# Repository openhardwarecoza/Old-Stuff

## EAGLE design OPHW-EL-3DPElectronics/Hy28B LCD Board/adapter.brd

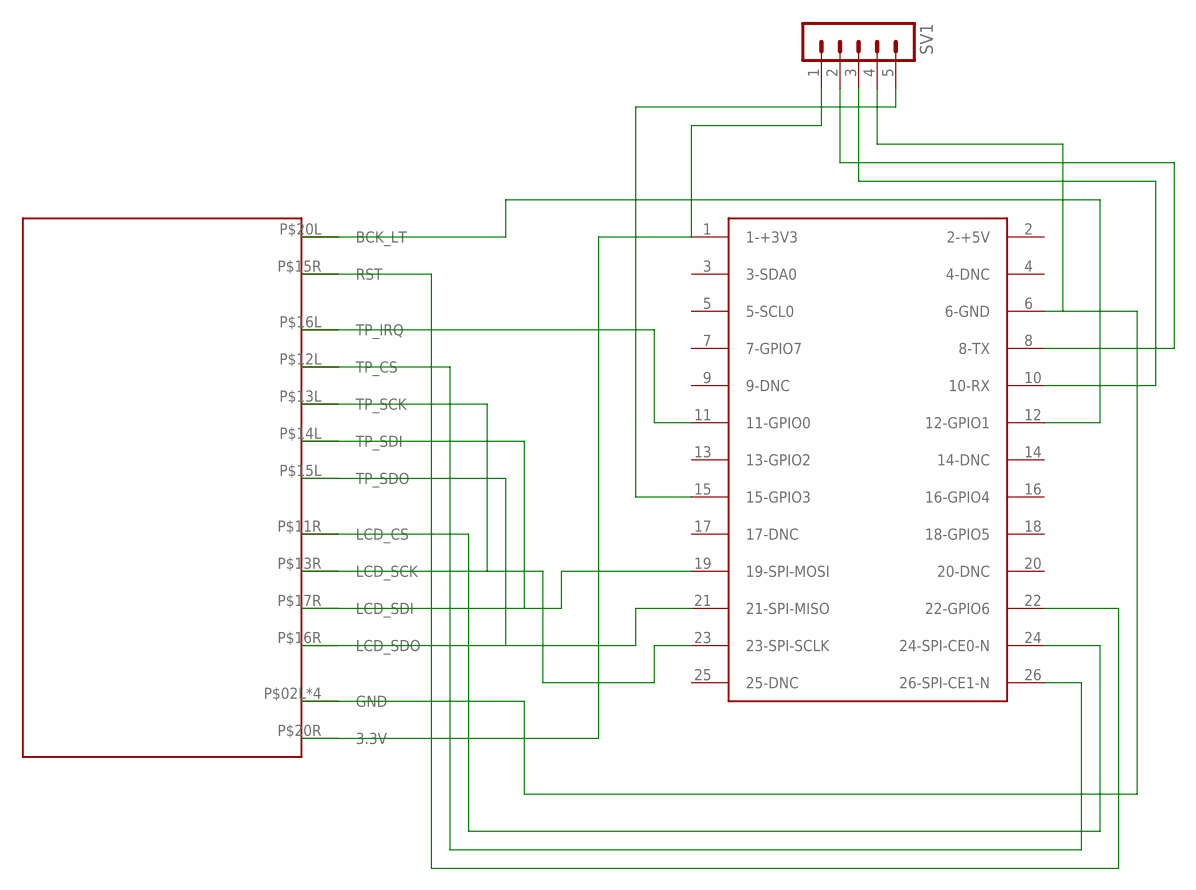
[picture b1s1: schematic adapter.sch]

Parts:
SV1: MA05-1
U$1: HY28BSTD; HY28B
U$2: RASPBERRY-PI

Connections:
unnamed: SV1.1, U$1.P$20R (3.3V), U$2.1 (1-+3V3)
unnamed: SV1.4, U$1.P$02L (GND), U$1.P$02R (GND), U$1.P$19L (GND), U$1.P$19R (GND), U$2.6 (6-GND)
unnamed: U$1.P$15L (TP_SDO), U$1.P$16R (LCD_SDO), U$2.21 (21-SPI-MISO)
unnamed: U$1.P$14L (TP_SDI), U$1.P$17R (LCD_SDI), U$2.19 (19-SPI-MOSI)
unnamed: U$1.P$13L (TP_SCK), U$1.P$13R (LCD_SCK), U$2.23 (23-SPI-SCLK)
unnamed: U$1.P$11R (LCD_CS), U$2.24 (24-SPI-CE0-N)
unnamed: U$1.P$12L (TP_CS), U$2.26 (26-SPI-CE1-N)
unnamed: U$1.P$16L (TP_IRQ), U$2.11 (11-GPIO0)
unnamed: U$1.P$20L (BCK_LT), U$2.12 (12-GPIO1)
unnamed: U$1.P$15R (RST), U$2.22 (22-GPIO6)
unnamed: SV1.2, U$2.8 (8-TX)
unnamed: SV1.3, U$2.10 (10-RX)
unnamed: SV1.5, U$2.15 (15-GPIO3)

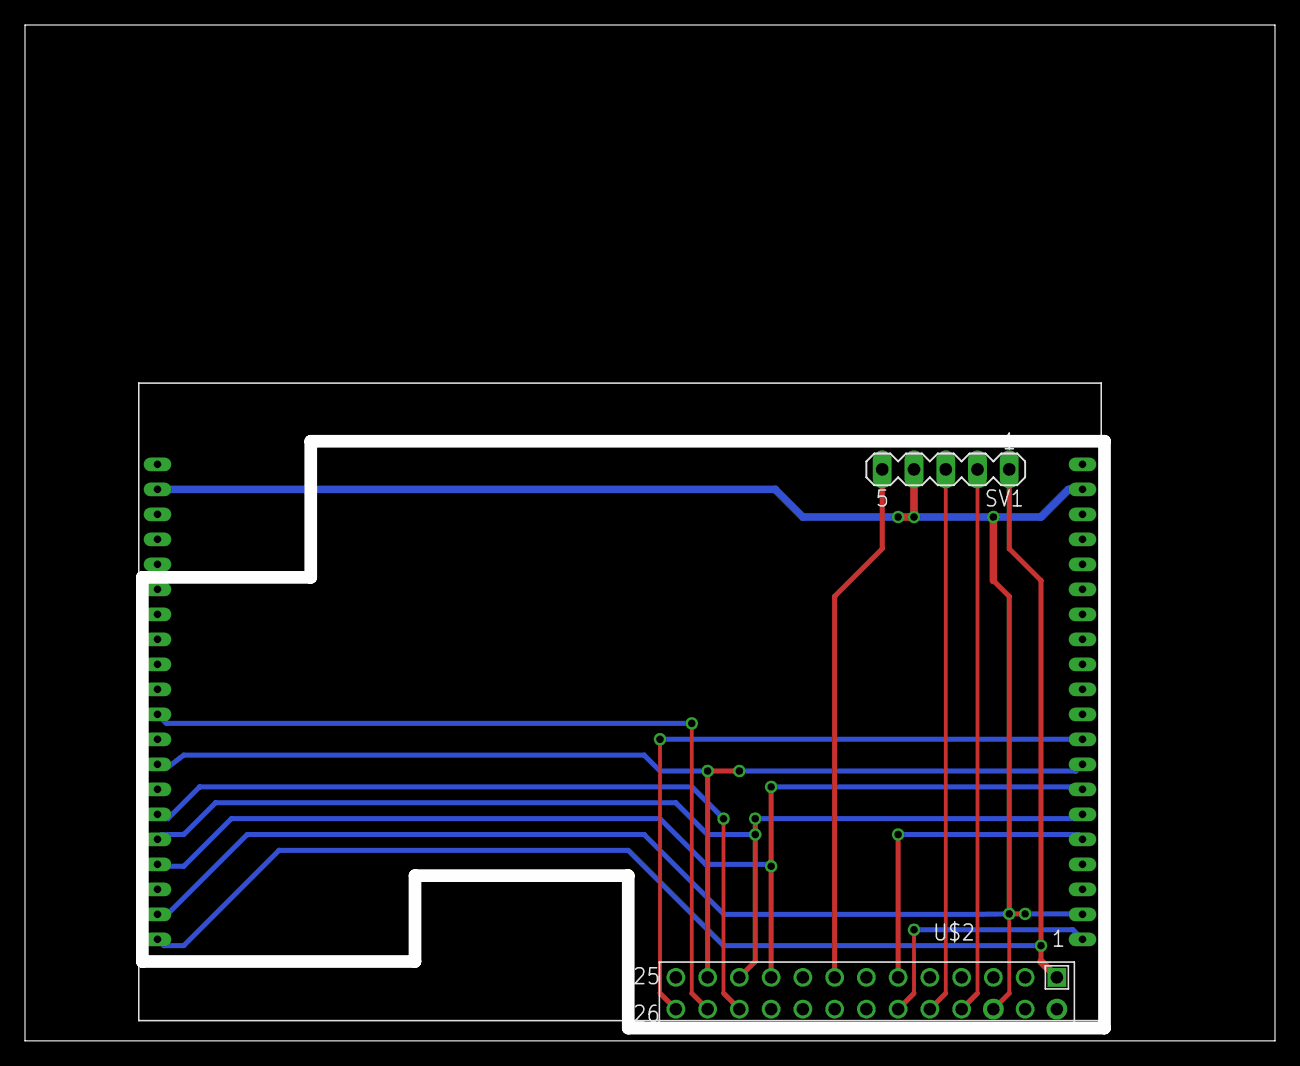
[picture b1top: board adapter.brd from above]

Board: 2 copper layers, 100.0 x 81.3 mm, 3 parts (0 on the bottom side), 13 nets.

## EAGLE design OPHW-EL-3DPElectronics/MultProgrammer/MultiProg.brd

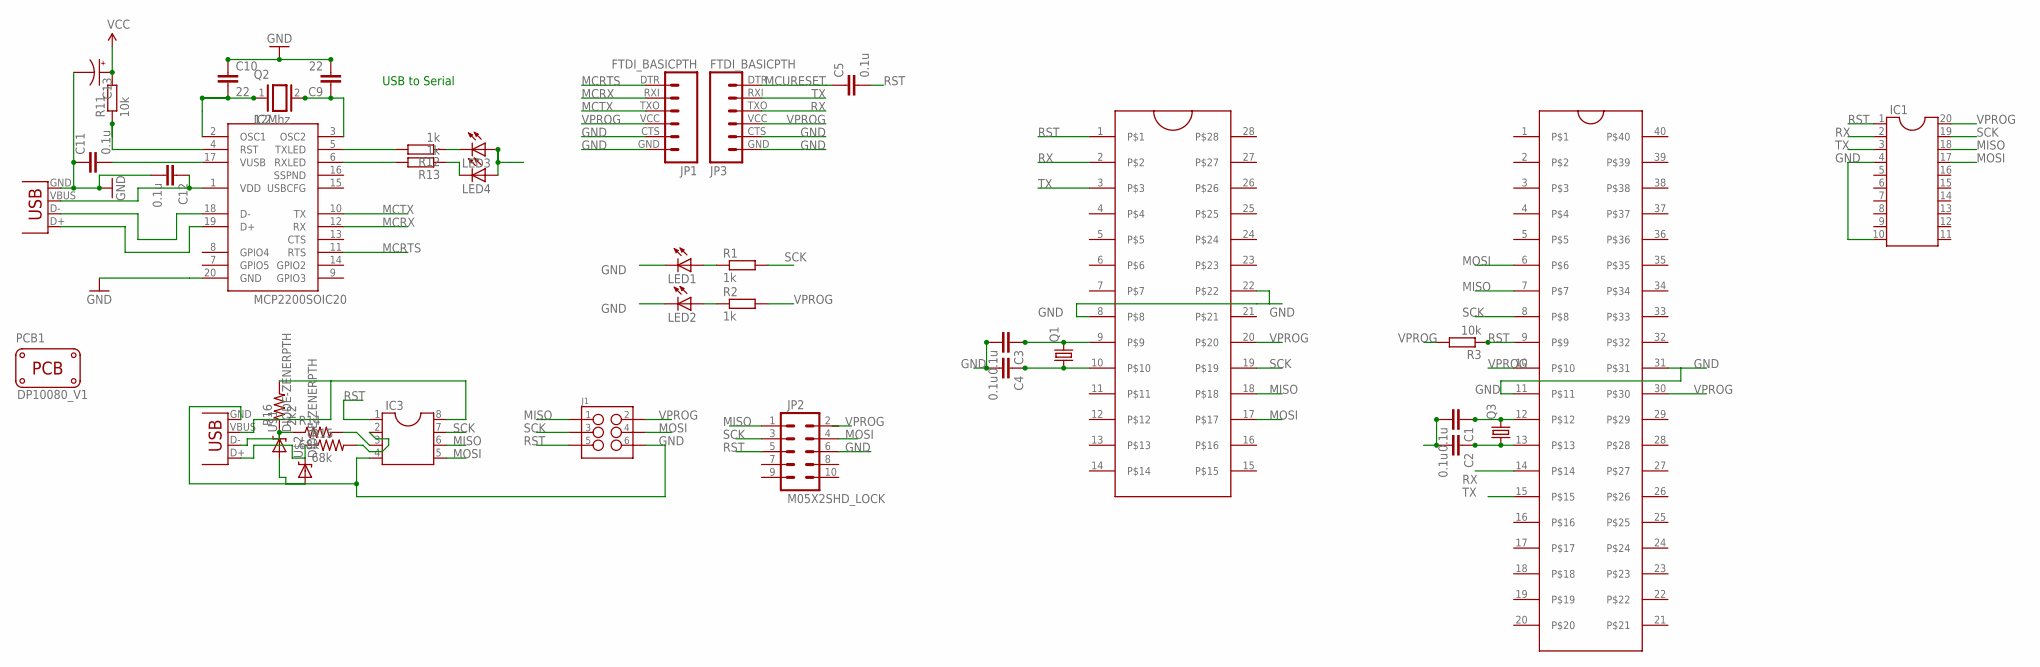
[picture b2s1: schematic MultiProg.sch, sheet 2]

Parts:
C1, C2, C3, C4, C5, C11, C12: 0.1u; CAP-PTH-SMALL-KIT
C9, C10: 22; CAP-PTH-SMALL-KIT
C13: CAP_POLPTH1; CPOL-RADIAL-100UF-25V
IC1: DIL20
IC2: MCP2200SOIC20; SOIC20
IC3: DIL8; DIL08
J1: M03X2SHROUD; 2X3-SHROUDED
JP1, JP3: FTDI_BASICPTH; FTDI_BASIC
JP2: M05X2SHD_LOCK; 2X5-SHROUDED_LOCK
LED1, LED2, LED3, LED4: LED3MM
PCB1: PCB_DP_RECTANGLE-80X100; DP10080_V1
Q1, Q3: CRYSTALHC49U70; HC49U70
Q2: 12Mhz; QS
R1, R2, R12, R13: 1k; 0204/7
R3, R11: 10k; 0204/7
R14, R15: 68k; 0204/7
R16: 2k2; 0204/7
U$1, U$2: DIODE-ZENERPTH; DIODE-ZENER
U$3: ZIFSOCKET-28-3ZIFFSOCKET-28-3; DIL28-3-ZIF_SOCKET
U$4: ZIFSOCKET-40-6DIL40-6-ZIF_SOCKET; DIL40-6-ZIF_SOCKET
X1, X3: USBPTH; USB-B-PTH

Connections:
D+: R15.1, U$2.P$1 (C), X3.D+
D-: R14.1, R16.1, U$1.P$1 (C), X3.D-
GND: C1.2, C2.2, C3.2, C4.2, C9.2, C10.1, C11.1, C12.2, C13.2 (-), IC1.4, IC1.10, IC2.20 (GND), IC3.4, J1.6, JP1.CTS (5), JP1.GND (6), JP2.6, JP3.CTS (5), JP3.GND (6), LED1.K (C), LED2.K (C), U$1.P$2 (A), U$2.P$2 (A), U$3.8, U$3.22, U$4.11, U$4.31, X1.GND, X3.GND
MCRTS: IC2.11 (RTS), JP1.DTR (1)
MCRX: IC2.12 (RX), JP1.RXI (2)
MCTX: IC2.10 (TX), JP1.TXO (3)
MCURESET: C5.1, JP3.DTR (1)
MISO: IC1.18, IC3.6, J1.1, JP2.1, U$3.18, U$4.7
MOSI: IC1.17, IC3.5, J1.4, JP2.4, U$3.17, U$4.6
unnamed: IC3.3, R14.2
unnamed: C10.2, IC2.2 (OSC1), Q2.1
unnamed: C9.1, IC2.3 (OSC2), Q2.2
unnamed: IC2.18 (D-), X1.D-
unnamed: IC2.19 (D+), X1.D+
unnamed: C11.2, IC2.17 (VUSB)
unnamed: IC2.5 (TXLED), R12.2
unnamed: IC2.6 (RXLED), R13.2
unnamed: LED3.K (C), R12.1
unnamed: LED4.K (C), R13.1
unnamed: IC2.4 (RST), R11.1
unnamed: IC3.2, R15.2
unnamed: LED2.A, R2.1
unnamed: LED1.A, R1.1
unnamed: C1.1, Q3.2, U$4.12
unnamed: C2.1, Q3.1, U$4.13
unnamed: C3.1, Q1.2, U$3.9
unnamed: C4.1, Q1.1, U$3.10
RST: C5.2, IC1.1, IC3.1, J1.5, JP2.5, R3.1, U$3.1, U$4.9
RX: IC1.2, JP3.TXO (3), U$3.2, U$4.14
SCK: IC1.19, IC3.7, J1.3, JP2.3, R1.2, U$3.19, U$4.8
TX: IC1.3, JP3.RXI (2), U$3.3, U$4.15
VBUS: C12.1, IC2.1 (VDD), LED3.A, LED4.A, X1.VBUS
VPROG: C13.1 (+), IC1.20, IC3.8, J1.2, JP1.VCC (4), JP3.VCC (4), R2.2, R3.2, R11.2, R16.2, U$3.20, U$4.10, U$4.30, X3.VBUS

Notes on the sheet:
USB to Serial

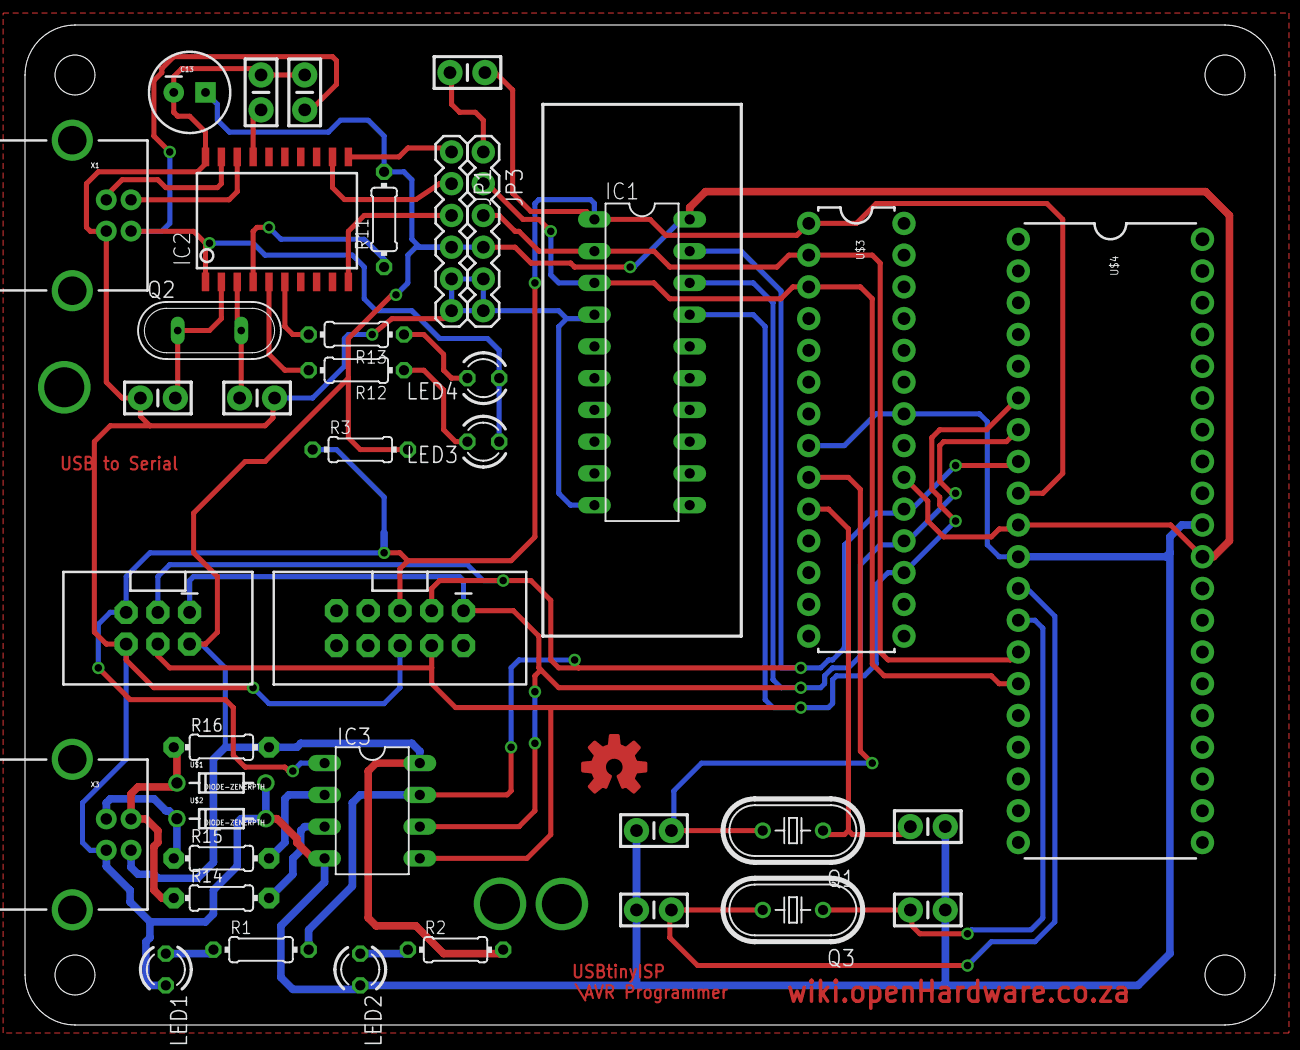
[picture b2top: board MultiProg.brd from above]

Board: 2 copper layers, 100.0 x 80.0 mm, 41 parts (0 on the bottom side), 33 nets.

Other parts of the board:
U$5: OSHWLOGO_TOP_0.2

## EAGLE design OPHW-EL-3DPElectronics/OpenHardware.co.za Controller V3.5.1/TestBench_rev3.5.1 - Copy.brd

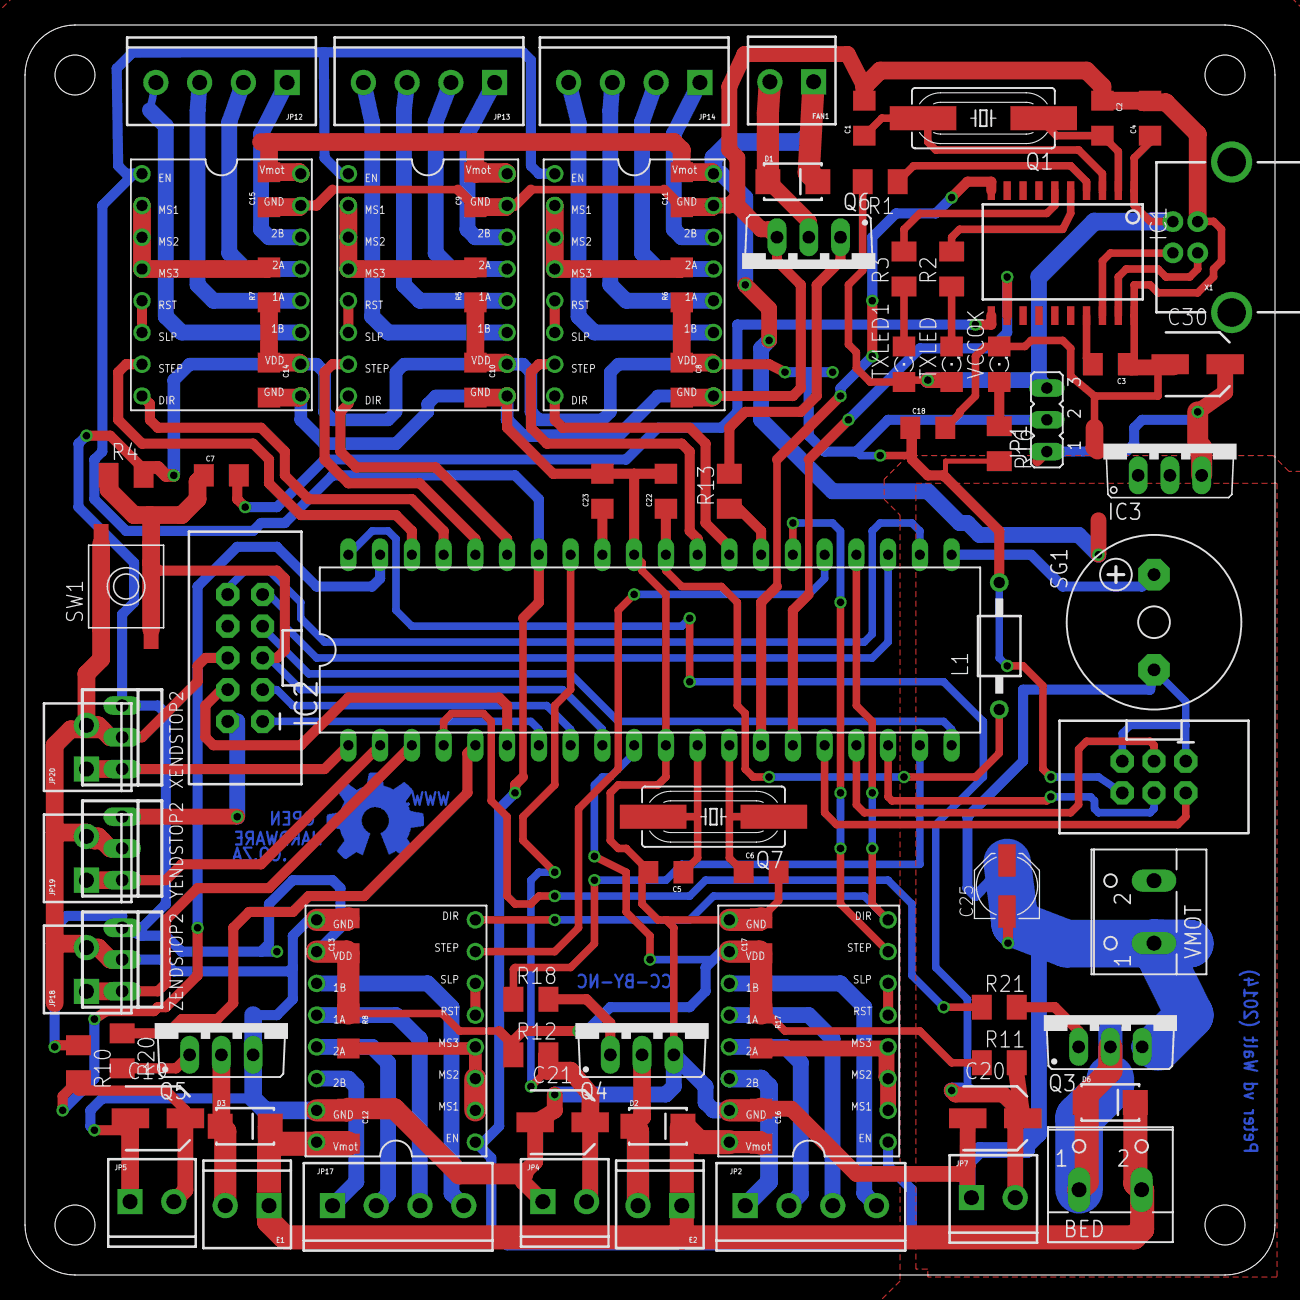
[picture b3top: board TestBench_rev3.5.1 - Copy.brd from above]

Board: 2 copper layers, 100.0 x 100.0 mm, 91 parts (0 on the bottom side), 92 nets.

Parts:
BED: W237-102
C1, C2, C5, C6: 22; 1206
C3, C4, C7, C18, C22, C23: 0.1u; 1206
C8, C9, C10, C11, C12, C13, C14, C15, C16, C17: 1206
C19, C20, C21, C30: 10u; SANYO-OSCON_SMD_B6
C25: 100u; PANASONIC_C
D1, D2, D3, D6: SMA-DIODE_ALT
E1: E1; SCREWTERMINAL-3.5MM-2
E1POL, E2POL: POLOLU_A4983CARRIER; A4988BREAKOUT
E2: E2; SCREWTERMINAL-3.5MM-2
FAN1: FAN; SCREWTERMINAL-3.5MM-2
IC1: MCP2200SOIC20; SOIC20
IC2: ATMEGA644-20PU; DIL40
IC3: 7805TV; TO220V
JP1: JP2
JP2, JP12, JP13, JP14, JP17: SCREWTERMINAL-3.5MM-4
JP3: 2X3-SHROUDED
JP4, JP5, JP7, JP18, JP19, JP20: SCREWTERMINAL-3.5MM-2
JP6: M05X2SHD_LOCK; 2X5-SHROUDED_LOCK
L1: 10uH; BL01RN1A
PCB1: PCB_DP_SQUARE-10X10; DP100100_V1
Q1: 12Mhz; HC49UP
Q3, Q4, Q5, Q6: TO220BV
Q7: 20Mhz; HC49UP
R1, R4: 10k; M1206
R2, R3, R16: 1k; M1206
R5, R6, R7, R8, R17: 1206
R10, R11, R12: 4k7; M1206
R13, R18, R20, R21: 10R; M1206
SG1: F/CM12P
SW1: SPST_TACT-EVQQ2; EVQ-Q2
TXLED, TXLED1: 1206
U$1: LABEL_JUMPER_1X3; JUMP3_DESC
VCCOK: 1206
VMOT: W237-102
X1: USBPTH; USB-B-PTH
XENDSTOP2: 22-23-2031
XPOL: POLOLU_A4983CARRIER; A4988BREAKOUT
YENDSTOP2: 22-23-2031
YPOL: POLOLU_A4983CARRIER; A4988BREAKOUT
ZENDSTOP2: 22-23-2031
ZPOL: POLOLU_A4983CARRIER; A4988BREAKOUT

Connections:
5VREG: C30.+, IC3.3, JP1.1
AVCC: C22.1, IC2.30, L1.1
BEDADC: C20.+, IC2.40, JP7.2, R11.2
BEDMSFT: IC2.4, R21.1
BEDOUT1: BED.1, D6.A, Q3.D
BEDOUT2: D3.A, E1.2, Q5.D
BUZZER: IC2.21, SG1.+
E1DIR: E1POL.DIR, E2POL.DIR, IC2.24
E1OUT1: D2.A, E2.2, Q4.D
E1STEP: E1POL.STEP, IC2.25
E2MSFT: IC2.19, R18.1
E2STEP: E2POL.STEP, IC2.26
ENABLE: E1POL.EN, E2POL.EN, IC2.34, XPOL.EN, YPOL.EN, ZPOL.EN
ENCA: IC2.16, JP3.2
ENCB: IC2.17, JP3.3
ENCC: IC2.18, JP3.4
EXT2ADC: C21.+, IC2.33, JP4.2, R12.2
EXTADC: C19.+, IC2.39, JP5.2, R10.2
EXTMSFT: IC2.5, R20.1
FANMSFT: IC2.27, R13.1
FANOUT1: D1.A, FAN1.2, Q6.D
GND: C1.2, C2.1, C3.1, C4.2, C5.2, C6.2, C8.2, C9.1, C10.2, C11.1, C12.1, C13.2, C14.2, C15.1, C16.1, C17.2, C18.2, C19.-, C20.-, C21.-, C22.2, C23.2, C25.-, C30.-, E1POL.GND, E1POL.GND@0, E2POL.GND, E2POL.GND@0, IC1.20, IC2.11, IC2.31, IC3.2, JP3.1, JP3.5, JP4.1, JP5.1, JP6.6, JP7.1, JP18.2, JP19.2, JP20.2, Q3.S, Q4.S, Q5.S, Q6.S, SG1.-, SW1.B, SW1.B', VCCOK.C, VMOT.1, X1.GND, XENDSTOP2.2, XPOL.GND, XPOL.GND@0, YENDSTOP2.2, YPOL.GND, YPOL.GND@0, ZENDSTOP2.2, ZPOL.GND, ZPOL.GND@0
MCRTS: C7.2, IC1.11
MCRX: IC1.12, IC2.15
MCTX: IC1.10, IC2.14
MCURESET: C7.1, IC2.9, JP6.5, R4.1, SW1.A, SW1.A'
MISO: IC2.7, JP6.1
MOSI: IC2.6, JP6.4
unnamed: C2.2, IC1.2, Q1.1
unnamed: C1.1, IC1.3, Q1.2
unnamed: IC1.5, R2.2
unnamed: IC1.18, X1.D-
unnamed: IC1.19, X1.D+
unnamed: IC1.6, R3.2
unnamed: C3.2, IC1.17
unnamed: E2POL.RST, E2POL.SLP
unnamed: R2.1, TXLED.C
unnamed: R3.1, TXLED1.C
unnamed: C5.1, IC2.12, Q7.2
unnamed: C6.1, IC2.13, Q7.1
unnamed: IC1.4, R1.1
unnamed: E1POL.RST, E1POL.SLP
unnamed: ZPOL.RST, ZPOL.SLP
unnamed: YPOL.RST, YPOL.SLP
unnamed: XPOL.RST, XPOL.SLP
unnamed: R7.2, XPOL.MS1, XPOL.MS2, XPOL.MS3
unnamed: R5.2, YPOL.MS1, YPOL.MS2, YPOL.MS3
unnamed: E1POL.MS1, E1POL.MS2, E1POL.MS3, R8.2
unnamed: R6.2, ZPOL.MS1, ZPOL.MS2, ZPOL.MS3
unnamed: E1POL.1B, JP17.4
unnamed: E1POL.1A, JP17.3
unnamed: E1POL.2A, JP17.2
unnamed: E1POL.2B, JP17.1
unnamed: JP14.4, ZPOL.1B
unnamed: JP14.3, ZPOL.1A
unnamed: JP14.2, ZPOL.2A
unnamed: JP14.1, ZPOL.2B
unnamed: JP13.1, YPOL.2B
unnamed: JP13.2, YPOL.2A
unnamed: JP13.3, YPOL.1A
unnamed: JP13.4, YPOL.1B
unnamed: JP12.4, XPOL.1B
unnamed: JP12.3, XPOL.1A
unnamed: JP12.2, XPOL.2A
unnamed: JP12.1, XPOL.2B
unnamed: E2POL.MS1, E2POL.MS2, E2POL.MS3, R17.2
unnamed: E2POL.1B, JP2.4
unnamed: E2POL.1A, JP2.3
unnamed: E2POL.2A, JP2.2
unnamed: E2POL.2B, JP2.1
unnamed: Q5.G, R20.2
unnamed: C23.1, IC2.32
unnamed: Q6.G, R13.2
unnamed: Q4.G, R18.2
unnamed: R16.1, VCCOK.A
unnamed: Q3.G, R21.2
SCK: IC2.8, JP6.3
SCL: IC2.22, JP6.10
SDA: IC2.23, JP6.9
SDS: IC2.20, JP6.7
VCC: C8.1, C10.1, C13.1, C14.1, C17.1, C18.1, E1POL.VDD, E2POL.VDD, IC2.10, JP1.2, JP3.6, JP6.2, L1.2, R4.2, R5.1, R6.1, R7.1, R8.1, R10.1, R11.1, R12.1, R16.2, R17.1, XENDSTOP2.1, XPOL.VDD, YENDSTOP2.1, YPOL.VDD, ZENDSTOP2.1, ZPOL.VDD
VMOT: BED.2, C9.2, C11.2, C12.2, C15.2, C16.2, C25.+, D1.C, D2.C, D3.C, D6.C, E1.1, E1POL.VMOT, E2.1, E2POL.VMOT, FAN1.1, IC3.1, VMOT.2, XPOL.VMOT, YPOL.VMOT, ZPOL.VMOT
VUSB: C4.1, IC1.1, JP1.3, R1.2, TXLED.A, TXLED1.A, X1.VBUS
XDIR: IC2.37, XPOL.DIR
XEND: IC2.1, JP20.1, XENDSTOP2.3
XSTEP: IC2.38, XPOL.STEP
YDIR: IC2.35, YPOL.DIR
YEND: IC2.2, JP19.1, YENDSTOP2.3
YSTEP: IC2.36, YPOL.STEP
ZDIR: IC2.28, ZPOL.DIR
ZEND: IC2.3, JP18.1, ZENDSTOP2.3
ZSTEP: IC2.29, ZPOL.STEP

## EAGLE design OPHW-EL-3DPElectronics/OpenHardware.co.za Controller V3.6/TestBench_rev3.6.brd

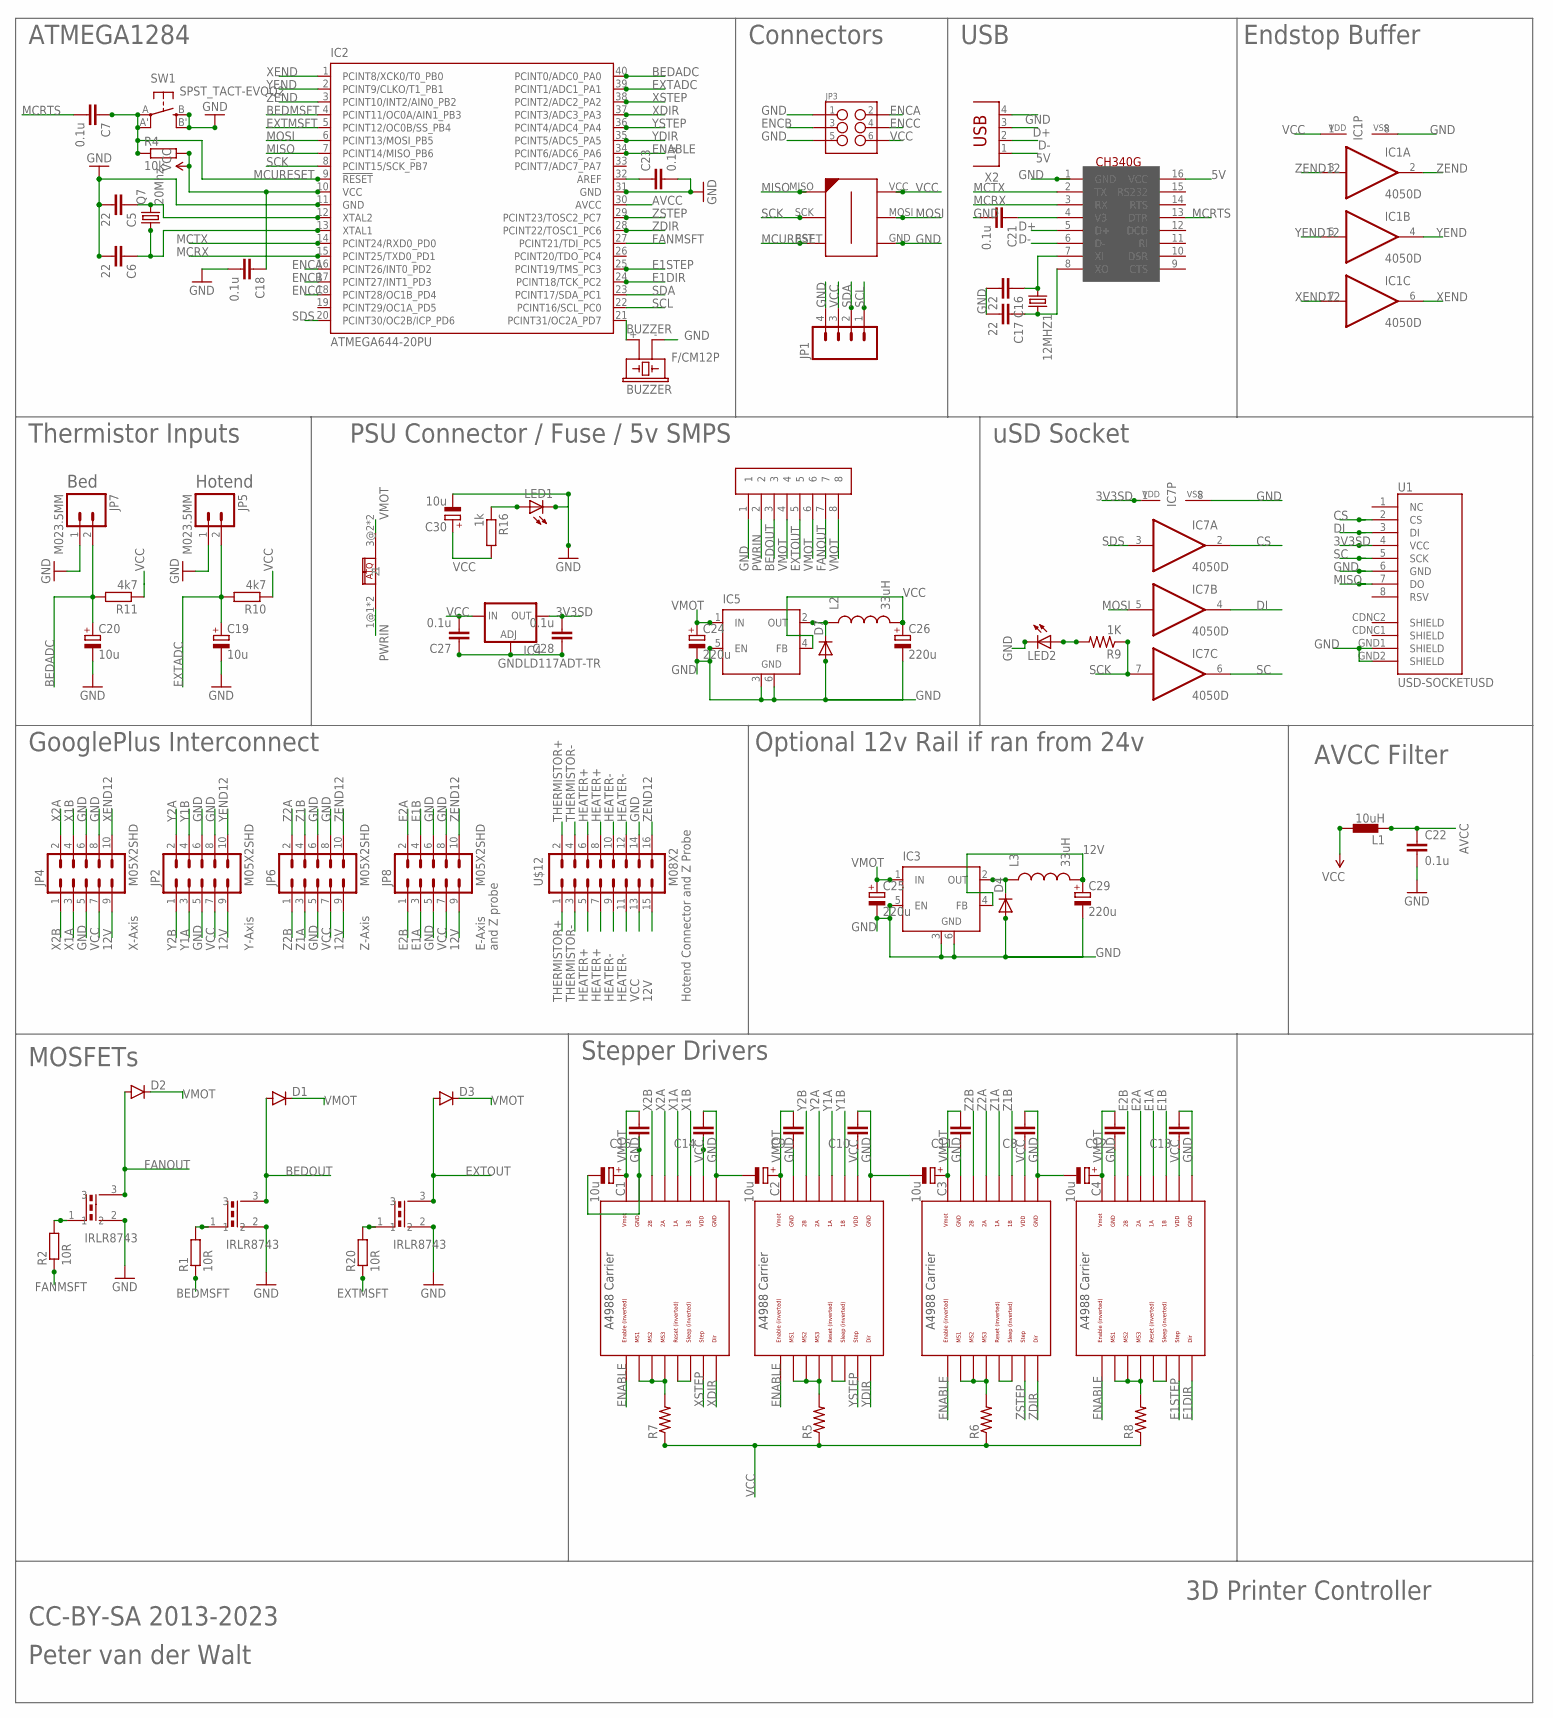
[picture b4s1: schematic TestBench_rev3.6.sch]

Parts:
12MHZ1: CRYSTALHC49UP; HC49UP
BUZZER: F/CM12P
C1, C2, C3, C4, C19, C20, C30: 10u; SANYO-OSCON_SMD_B6
C5, C6, C16, C17: 22; 1206
C7, C18, C21, C22, C23, C27, C28: 0.1u; 1206
C8, C9, C10, C11, C12, C13, C14, C15: CAP1206; 1206
C24, C25, C26, C29: 220u; 153CLV-0605
D1, D2, D3: DIODESMA-ALT; SMA-DIODE_ALT
D4, D7: DIODE-DO-214AC; DO-214AC
E1POL: POLOLU_A4983CARRIER; A4988BREAKOUT
IC1, IC7: 4050D; SO16
IC2: ATMEGA644-20PU; DIL40
IC3, IC5: LM2596S; TO263-5
IC4: LD117ADT-TR; DPACK
JP1: M04LOCK; 1X04_LOCK
JP2, JP4, JP6, JP8: M05X2SHD; 2X5-SHROUDED
JP3: M03X2SHROUD; 2X3-SHROUDED
JP5, JP7: M023.5MM; SCREWTERMINAL-3.5MM-2
L1: 10uH; BL01RN1A
L2, L3: 33uH; CDRH125
LED1, LED2: LEDSMT1206; 1206
Q7: 20Mhz; HC49UP
R1, R2, R20: 10R; M1206
R4: 10k; M1206
R5, R6, R7, R8: RESISTOR1206; 1206
R9: 1K; M1206
R10, R11: 4k7; M1206
R16: 1k; M1206
SW1: SPST_TACT-EVQQ2; EVQ-Q2
U1: USD-SOCKETUSD; USD-SOCKET-PP
U$1, U$3, U$4: IRLR8743; TO263
U$2: CH340G; SOIC16
U$5: XY825A-8P
U$6: CQ-121; CQ121
U$7: AVR-ISP-6-EDGE; 6PAD_ISP
U$12: M08X2; 2X8
X2: PN61729
XPOL: POLOLU_A4983CARRIER; A4988BREAKOUT
YPOL: POLOLU_A4983CARRIER; A4988BREAKOUT
ZPOL: POLOLU_A4983CARRIER; A4988BREAKOUT

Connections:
3V3SD: C28.2, IC4.4 (OUT), IC7.1 (VDD), U1.4 (VCC)
5V: U$2.16 (VCC), X2.1
12V: C29.+, IC3.4 (FB), JP2.9, JP4.9, JP6.9, JP8.9, L3.2, U$12.15
AVCC: C22.1, IC2.30 (AVCC), L1.1
BEDADC: C20.+, IC2.40 (PCINT0/ADC0_PA0), JP7.2, R11.2
BEDMSFT: IC2.4 (PCINT11/OC0A/AIN1_PB3), R1.1
BEDOUT: D1.A, U$3.3, U$5.3
BUZZER: BUZZER.+ (1), IC2.21 (PCINT31/OC2A_PD7)
CS: IC7.2 (O), U1.2 (CS)
D+: U$2.5 (D+), X2.3
D-: U$2.6 (D-), X2.2
DI: IC7.4 (O), U1.3 (DI)
E1A: E1POL.1A, JP8.3
E1B: E1POL.1B, JP8.4
E1DIR: E1POL.DIR, IC2.24 (PCINT18/TCK_PC2)
E1STEP: E1POL.STEP, IC2.25 (PCINT19/TMS_PC3)
E2A: E1POL.2A, JP8.2
E2B: E1POL.2B, JP8.1
ENABLE: E1POL.EN, IC2.34 (PCINT6/ADC6_PA6), XPOL.EN, YPOL.EN, ZPOL.EN
ENCA: IC2.16 (PCINT26/INT0_PD2), JP3.2
ENCB: IC2.17 (PCINT27/INT1_PD3), JP3.3
ENCC: IC2.18 (PCINT28/OC1B_PD4), JP3.4
EXTADC: C19.+, IC2.39 (PCINT1/ADC1_PA1), JP5.2, R10.2
EXTMSFT: IC2.5 (PCINT12/OC0B/SS_PB4), R20.1
EXTOUT: D3.A, U$1.3, U$5.5
FANMSFT: IC2.27 (PCINT21/TDI_PC5), R2.1
FANOUT: D2.A, U$4.3, U$5.7
GND: BUZZER.- (2), C1.-, C2.-, C3.-, C4.-, C5.2, C6.2, C8.2, C9.1, C10.2, C11.1, C12.1, C13.2, C14.2, C15.1, C16.2, C17.2, C18.2, C19.-, C20.-, C21.2, C22.2, C23.2, C24.-, C25.-, C26.-, C27.1, C28.1, C29.-, C30.-, D4.2 (A), D7.2 (A), E1POL.GND, E1POL.GND@0 (GND), IC1.8 (VSS), IC2.11 (GND), IC2.31 (GND), IC3.3 (GND), IC3.5 (EN), IC3.6 (GND), IC4.1 (ADJ), IC5.3 (GND), IC5.5 (EN), IC5.6 (GND), IC7.8 (VSS), JP1.4, JP2.5, JP2.6, JP2.8, JP3.1, JP3.5, JP4.5, JP4.6, JP4.8, JP5.1, JP6.5, JP6.6, JP6.8, JP7.1, JP8.5, JP8.6, JP8.8, LED1.C, LED2.C, SW1.B (S), SW1.B' (S1), U1.6 (GND), U1.GND1 (SHIELD), U1.GND2 (SHIELD), U$1.2 (1), U$2.1 (GND), U$3.2 (1), U$4.2 (1), U$5.1, U$7.GND, U$12.14, X2.4, XPOL.GND, XPOL.GND@0 (GND), YPOL.GND, YPOL.GND@0 (GND), ZPOL.GND, ZPOL.GND@0 (GND)
HEATER+: U$12.5, U$12.6, U$12.7, U$12.8
HEATER-: U$12.9, U$12.10, U$12.11, U$12.12
MCRTS: C7.2, U$2.13 (DTR)
MCRX: IC2.15 (PCINT25/TXD0_PD1), U$2.3 (RX)
MCTX: IC2.14 (PCINT24/RXD0_PD0), U$2.2 (TX)
MCURESET: C7.1, IC2.9 (!RESET), R4.1, SW1.A, SW1.A' (P1), U$7.RST
MISO: IC2.7 (PCINT14/MISO_PB6), U1.7 (DO), U$7.MISO
MOSI: IC2.6 (PCINT13/MOSI_PB5), IC7.5 (I), U$7.MOSI
unnamed: D4.1 (C), IC3.2 (OUT), L3.1
unnamed: R1.2, U$3.1 (2)
unnamed: R2.2, U$4.1 (2)
unnamed: D7.1 (C), IC5.2 (OUT), L2.1
unnamed: C5.1, IC2.12 (XTAL2), Q7.2
unnamed: C6.1, IC2.13 (XTAL1), Q7.1
unnamed: E1POL.RST, E1POL.SLP (SLEEP)
unnamed: ZPOL.RST, ZPOL.SLP (SLEEP)
unnamed: YPOL.RST, YPOL.SLP (SLEEP)
unnamed: XPOL.RST, XPOL.SLP (SLEEP)
unnamed: R7.2, XPOL.MS1, XPOL.MS2, XPOL.MS3
unnamed: R5.2, YPOL.MS1, YPOL.MS2, YPOL.MS3
unnamed: E1POL.MS1, E1POL.MS2, E1POL.MS3, R8.2
unnamed: R6.2, ZPOL.MS1, ZPOL.MS2, ZPOL.MS3
unnamed: 12MHZ1.1, C16.1, U$2.7 (XI)
unnamed: LED2.A, R9.2
unnamed: 12MHZ1.2, C17.1, U$2.8 (XO)
unnamed: C21.1, U$2.4 (V3)
unnamed: R20.2, U$1.1 (2)
unnamed: C23.1, IC2.32 (AREF)
unnamed: LED1.A, R16.1
PWRIN: U$5.2, U$6.1@1 (1), U$6.2@1 (1)
SC: IC7.6 (O), U1.5 (SCK)
SCK: IC2.8 (PCINT15/SCK_PB7), IC7.7 (I), R9.1, U$7.SCK
SCL: IC2.22 (PCINT16/SCL_PC0), JP1.1
SDA: IC2.23 (PCINT17/SDA_PC1), JP1.2
SDS: IC2.20 (PCINT30/OC2B/ICP_PD6), IC7.3 (I)
THERMISTOR+: U$12.1, U$12.2
THERMISTOR-: U$12.3, U$12.4
VCC: C8.1, C10.1, C13.1, C14.1, C18.1, C26.+, C27.2, C30.+, E1POL.VDD, IC1.1 (VDD), IC2.10 (VCC), IC4.3 (IN), IC5.4 (FB), JP1.3, JP2.7, JP3.6, JP4.7, JP6.7, JP8.7, L1.2, L2.2, R4.2, R5.1, R6.1, R7.1, R8.1, R10.1, R11.1, R16.2, U$7.VCC, U$12.13, XPOL.VDD, YPOL.VDD, ZPOL.VDD
VMOT: C1.+, C2.+, C3.+, C4.+, C9.2, C11.2, C12.2, C15.2, C24.+, C25.+, D1.C, D2.C, D3.C, E1POL.VMOT, IC3.1 (IN), IC5.1 (IN), U$5.4, U$5.6, U$5.8, U$6.3@2 (2), U$6.4@2 (2), XPOL.VMOT, YPOL.VMOT, ZPOL.VMOT
X1A: JP4.3, XPOL.1A
X1B: JP4.4, XPOL.1B
X2A: JP4.2, XPOL.2A
X2B: JP4.1, XPOL.2B
XDIR: IC2.37 (PCINT3/ADC3_PA3), XPOL.DIR
XEND: IC1.6 (O), IC2.1 (PCINT8/XCK0/T0_PB0)
XEND12: IC1.7 (I), JP4.10
XSTEP: IC2.38 (PCINT2/ADC2_PA2), XPOL.STEP
Y1A: JP2.3, YPOL.1A
Y1B: JP2.4, YPOL.1B
Y2A: JP2.2, YPOL.2A
Y2B: JP2.1, YPOL.2B
YDIR: IC2.35 (PCINT5/ADC5_PA5), YPOL.DIR
YEND: IC1.4 (O), IC2.2 (PCINT9/CLKO/T1_PB1)
YEND12: IC1.5 (I), JP2.10
YSTEP: IC2.36 (PCINT4/ADC4_PA4), YPOL.STEP
Z1A: JP6.3, ZPOL.1A
Z1B: JP6.4, ZPOL.1B
Z2A: JP6.2, ZPOL.2A
Z2B: JP6.1, ZPOL.2B
ZDIR: IC2.28 (PCINT22/TOSC1_PC6), ZPOL.DIR
ZEND: IC1.2 (O), IC2.3 (PCINT10/INT2/AIN0_PB2)
ZEND12: IC1.3 (I), JP6.10, JP8.10, U$12.16
ZSTEP: IC2.29 (PCINT23/TOSC2_PC7), ZPOL.STEP

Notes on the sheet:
Thermistor Inputs
Stepper Drivers
AVCC Filter
PSU Connector / Fuse / 5v SMPS
MOSFETs
ATMEGA1284
CC-BY-SA 2013-2023
Peter van der Walt
3D Printer Controller
USB
Connectors
uSD Socket
Bed
Hotend
Optional 12v Rail if ran from 24v
X-Axis
Y-Axis
Z-Axis
E-Axis
Endstop Buffer
GooglePlus Interconnect
and Z probe
Hotend Connector and Z Probe

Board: 2 copper layers, 84 parts (0 on the bottom side), 91 nets, no tracks yet.

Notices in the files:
OPHW-EL-3DPElectronics/OpenHardware.co.za Controller V3.5.1/TestBench_rev3.5.1 - Copy.brd:
CC-BY-NC
parts and their libraries:
SparkFun-Passives: Licensing: CC v3.0 Share-Alike You are welcome to use this library for commercial purposes.
